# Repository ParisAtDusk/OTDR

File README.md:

# OTDR

> Optical Time Domain Reflectometer.

## About

TODO

## Features

- TODO

## Requirements

- TODO

## Project Status

Early development. Interfaces, architecture, and documentation are subject to change.

## License

TODO

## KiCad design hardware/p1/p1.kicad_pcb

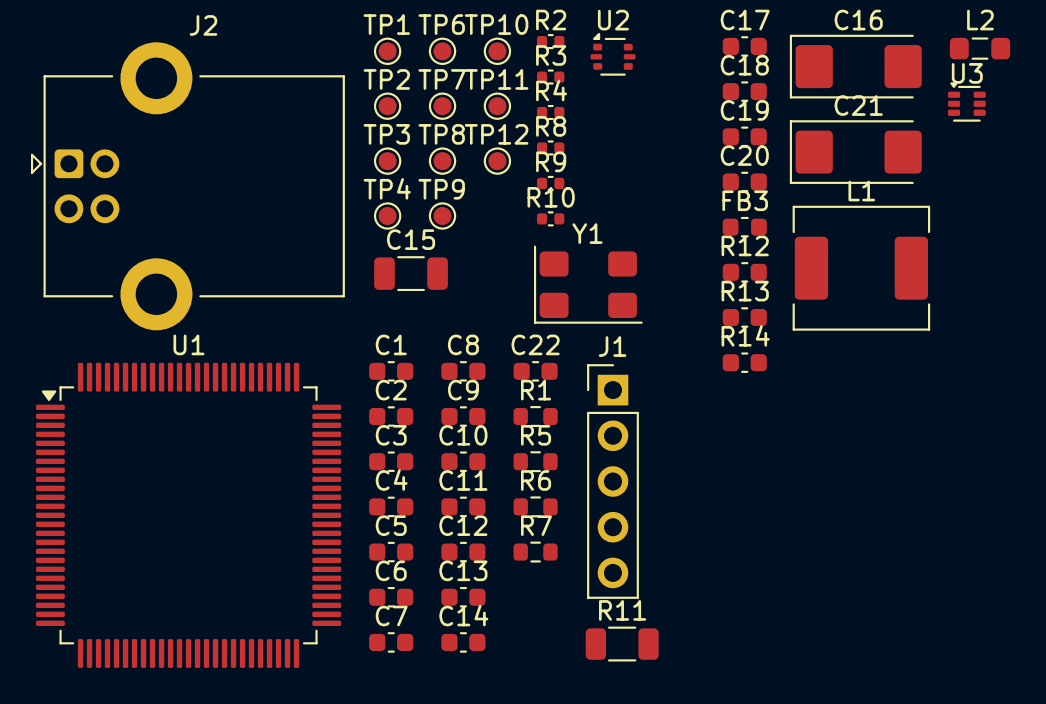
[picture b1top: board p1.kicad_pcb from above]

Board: 2 copper layers, 56 parts (0 on the bottom side), 37 nets, no tracks yet.

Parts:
C1, C2, C3, C4, C5, C6, C12, C17: 100n; C_0603_1608Metric
C7, C8, C9, C10, C11, C18: 2u2; C_0603_1608Metric
C13, C14: 12p; C_0603_1608Metric
C15: 2n2/2kV; C_1206_3216Metric
C16, C21: 47u; CP_EIA-6032-28_Kemet-C
C19, C20: 4u7; C_0603_1608Metric
C22: 10n; C_0603_1608Metric
FB3: BLM18PG600; L_0603_1608Metric
J1: Conn_01x05_Socket; PinHeader_1x05_P2.54mm_Vertical
J2: USB_B; USB_B_Lumberg_2411_02_Horizontal
L1: MPX1D0618L1R0; L_AVX_LMLP07A7
L2: LQM21PN2R2MGHL; L_0805_2012Metric_Pad1.05x1.20mm_HandSolder
R1: 10k; R_0603_1608Metric
R2, R3, R4, R8, R9, R10: 0R; C_0402_1005Metric
R5, R6, R7: 47R; R_0603_1608Metric
R11: 1M; R_1206_3216Metric
R12, R13, R14: 100k; C_0603_1608Metric
TP1, TP2, TP3, TP4, TP6, TP7, TP8, TP9, TP10, TP11, TP12: TestPoint; TestPoint_Pad_D1.0mm
U1: STM32H733VGTx; LQFP-100_14x14mm_P0.5mm
U2: USBLC6-2P6; SOT-666
U3: AP61300Z6; SOT-563
Y1: 25MHz; Crystal_SMD_WE_CFPX-104-4Pin_5.0x3.2mm

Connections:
/Power/GND: C16.2, C17.2, C18.2, C19.2, C20.2, C21.2, R14.1, U3.2 (GND)
/uC/+3V3: C8.1, C9.2, C21.1, J1.1, L2.2
/uC/ADC_CH1+: TP8.1 (1_1), U1.30 (PA6)
/uC/ADC_CH1-: TP9.1 (1_1), U1.31 (PA7)
/uC/ADC_CH2+: TP10.1 (1_1), U1.32 (PC4)
/uC/ADC_CH2-: TP11.1 (1_1), U1.33 (PC5)
/uC/ADC_TRIGGER: TP7.1 (1_1), U1.23 (PA1)
/uC/ADC_VREF: C12.2, R8.2, U1.20 (VREF+)
/uC/BOOT0: R2.2, R3.2, U1.94 (BOOT0)
/uC/LASER_EN: TP6.1 (1_1), U1.22 (PA0)
/uC/NRST: C22.2, R1.2, R7.1, U1.14 (NRST)
/uC/SWCLK: R5.1, U1.76 (PA14(JTCK)
/uC/SWDIO: R6.1, U1.72 (PA13(JTMS)
/uC/USB+: R9.2, U2.1 (I/O1)
/uC/USB-: R10.2, U2.3 (I/O2)
/uC/USB_SHLD: C15.1, J2.SH (Shield), R11.1
/uC/USB_VBUS: C16.1, FB3.1, J2.1 (VBUS), TP1.1 (1_1), U2.5 (VBUS)
/uC/VBAT: R4.1, TP12.1 (1_1), U1.6 (VBAT)
/uC/VCAP1: C11.1, U1.48 (VCAP)
/uC/VCAP2: C10.1, U1.73 (VCAP)
/uC/XTAL1_IN: C13.1, U1.12 (PH0), Y1.1
/uC/XTAL1_OUT: C14.1, U1.13 (PH1), Y1.3
/uC/uC_USB_D+: R9.1, U1.71 (PA12)
/uC/uC_USB_D-: R10.1, U1.70 (PA11)
/uC/uC_VDD: C1.2, C2.2, C3.2, C4.2, C5.2, R1.1, R2.1, R4.2, TP4.1 (1_1), U1.11 (VDD), U1.27 (VDD), U1.50 (VDD), U1.75 (VDD), U1.100 (VDD)
/uC/uC_VDDA: C6.2, C7.2, R8.1, TP3.1 (1_1), U1.21 (VDDA)
GND: C1.1, C2.1, C3.1, C4.1, C5.1, C6.1, C7.1, C8.2, C9.1, C10.2, C11.2, C12.1, C13.2, C14.2, C15.2, C22.1, J1.3, J2.4 (GND), R3.1, R11.2, TP2.1 (1_1), U1.10 (VSS), U1.19 (VSSA), U1.26 (VSS), U1.49 (VSS), U1.74 (VSS), U1.99 (VSS), U2.2 (GND), Y1.2 (G), Y1.4 (G)
unnamed: J1.2, R5.2
unnamed: J1.4, R6.2
unnamed: J1.5, R7.2
unnamed: J2.3 (D+), U2.6 (I/O1)
unnamed: J2.2 (D-), U2.4 (I/O2)
unnamed: R12.2, U3.5 (EN)
unnamed: R13.1, R14.2, U3.1 (FB)
unnamed: C19.1, C20.1, L1.2, L2.1, R13.2, U3.6 (OUT)
unnamed: L1.1, U3.4 (SW)
unnamed: C17.1, C18.1, FB3.2, R12.1, U3.3 (VIN)
